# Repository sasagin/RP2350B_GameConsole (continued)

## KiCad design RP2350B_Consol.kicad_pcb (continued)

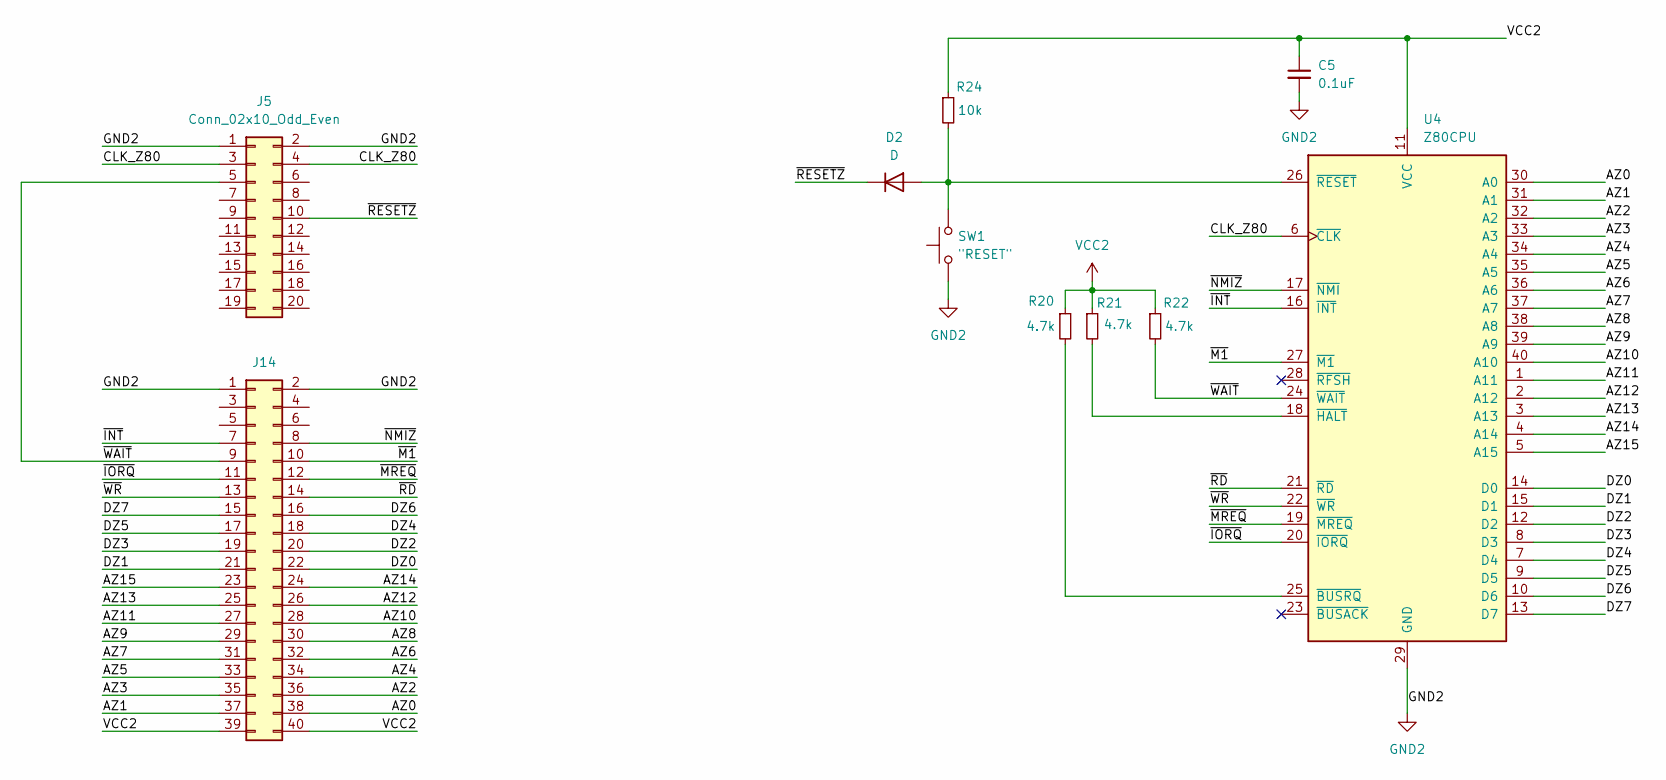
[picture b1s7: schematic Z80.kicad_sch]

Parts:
C5: 0.1uF; C_0805_2012Metric_Pad1.18x1.45mm_HandSolder
D2: D; D_1206_3216Metric_Pad1.42x1.75mm_HandSolder
J5: Conn_02x10_Odd_Even; EDGE_2x10
J14: Conn_02x20_Odd_Even; EDGE_2x20
R20, R21, R22: 4.7k; R_0805_2012Metric_Pad1.20x1.40mm_HandSolder
R24: 10k; R_0805_2012Metric_Pad1.20x1.40mm_HandSolder
SW1: "RESET"; SW_Tactile_SPST_Angled_PTS645Vx31-2LFS
U4: Z80CPU; DIP-40_W15.24mm_Socket

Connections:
/Z80/AZ0: J14.38, U4.30 (A0)
/Z80/AZ1: J14.37, U4.31 (A1)
/Z80/AZ2: J14.36, U4.32 (A2)
/Z80/AZ3: J14.35, U4.33 (A3)
/Z80/AZ4: J14.34, U4.34 (A4)
/Z80/AZ5: J14.33, U4.35 (A5)
/Z80/AZ6: J14.32, U4.36 (A6)
/Z80/AZ7: J14.31, U4.37 (A7)
/Z80/AZ8: J14.30, U4.38 (A8)
/Z80/AZ9: J14.29, U4.39 (A9)
/Z80/AZ10: J14.28, U4.40 (A10)
/Z80/AZ11: J14.27, U4.1 (A11)
/Z80/AZ12: J14.26, U4.2 (A12)
/Z80/AZ13: J14.25, U4.3 (A13)
/Z80/AZ14: J14.24, U4.4 (A14)
/Z80/AZ15: J14.23, U4.5 (A15)
/Z80/CLK_Z80: J5.3, J5.4, U4.6 (~CLK)
/Z80/DZ0: J14.22, U4.14 (D0)
/Z80/DZ1: J14.21, U4.15 (D1)
/Z80/DZ2: J14.20, U4.12 (D2)
/Z80/DZ3: J14.19, U4.8 (D3)
/Z80/DZ4: J14.18, U4.7 (D4)
/Z80/DZ5: J14.17, U4.9 (D5)
/Z80/DZ6: J14.16, U4.10 (D6)
/Z80/DZ7: J14.15, U4.13 (D7)
/Z80/~INT: J14.7, U4.16 (~INT)
/Z80/~IORQ: J14.11, U4.20 (~IORQ)
/Z80/~M1: J14.10, U4.27 (~M1)
/Z80/~MREQ: J14.12, U4.19 (~MREQ)
/Z80/~NMIZ: J14.8, U4.17 (~NMI)
/Z80/~RD: J14.14, U4.21 (~RD)
/Z80/~RESETZ: D2.1 (K), J5.10
/Z80/~WAIT: J5.5, J14.9, R22.2, U4.24 (~WAIT)
/Z80/~WR: J14.13, U4.22 (~WR)
GND2: C5.2, J5.1, J5.2, J14.1, J14.2, SW1.1, U4.29 (GND)
unnamed: D2.2 (A), R24.2, SW1.2, U4.26 (~RESET)
unnamed: R20.2, U4.25 (~BUSRQ)
unnamed: R21.2, U4.18 (~HALT)
VCC2: C5.1, J14.39, J14.40, R20.1, R21.1, R22.1, R24.1, U4.11 (VCC)

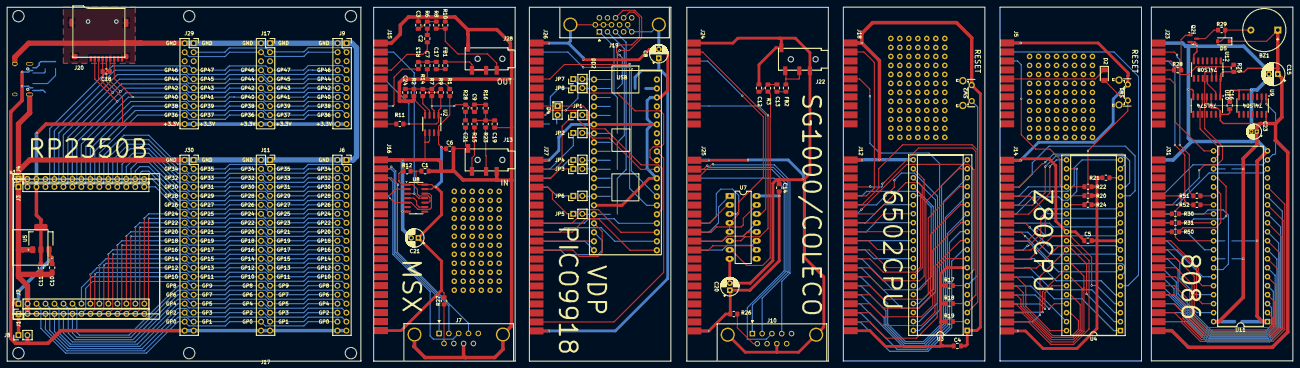
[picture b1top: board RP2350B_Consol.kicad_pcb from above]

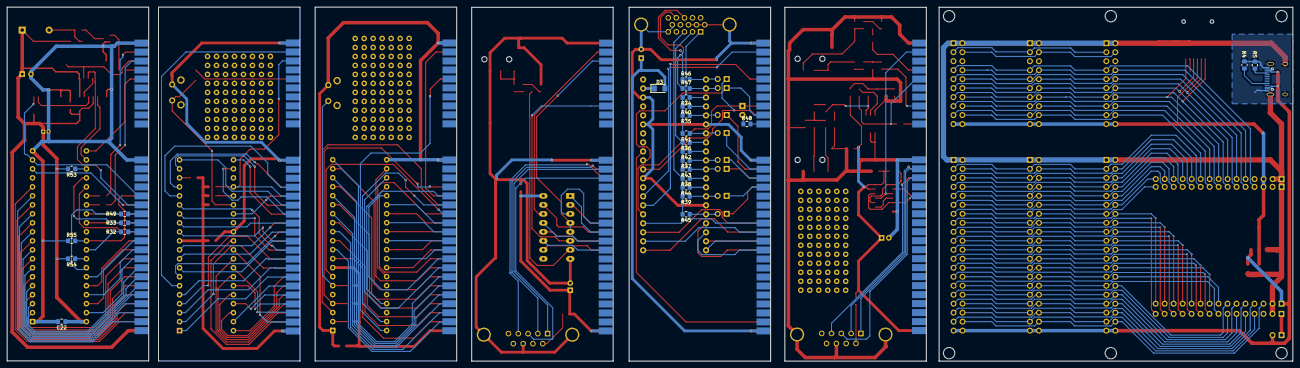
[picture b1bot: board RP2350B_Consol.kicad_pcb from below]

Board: 2 copper layers, 363.4 x 100.1 mm, 142 parts (26 on the bottom side), 282 nets.

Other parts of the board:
C21#2: 0.022; C_0805_2012Metric_Pad1.18x1.45mm_HandSolder
R28#2: 4.7k; R_0805_2012Metric_Pad1.20x1.40mm_HandSolder

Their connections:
GND_MSX: C21#2.2; also elsewhere on the board
unnamed: C21#2.1, R28#2.1
unnamed 262: R28#2.2; also elsewhere on the board

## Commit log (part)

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2026-02-21 Create README.md
    RP2350B + Z80 + MOS6502
